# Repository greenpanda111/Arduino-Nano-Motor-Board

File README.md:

# Arduino-Nano-Motor-Board
A breakout board for an Arduino nano 33 BLE with motor controller and UART to serial port

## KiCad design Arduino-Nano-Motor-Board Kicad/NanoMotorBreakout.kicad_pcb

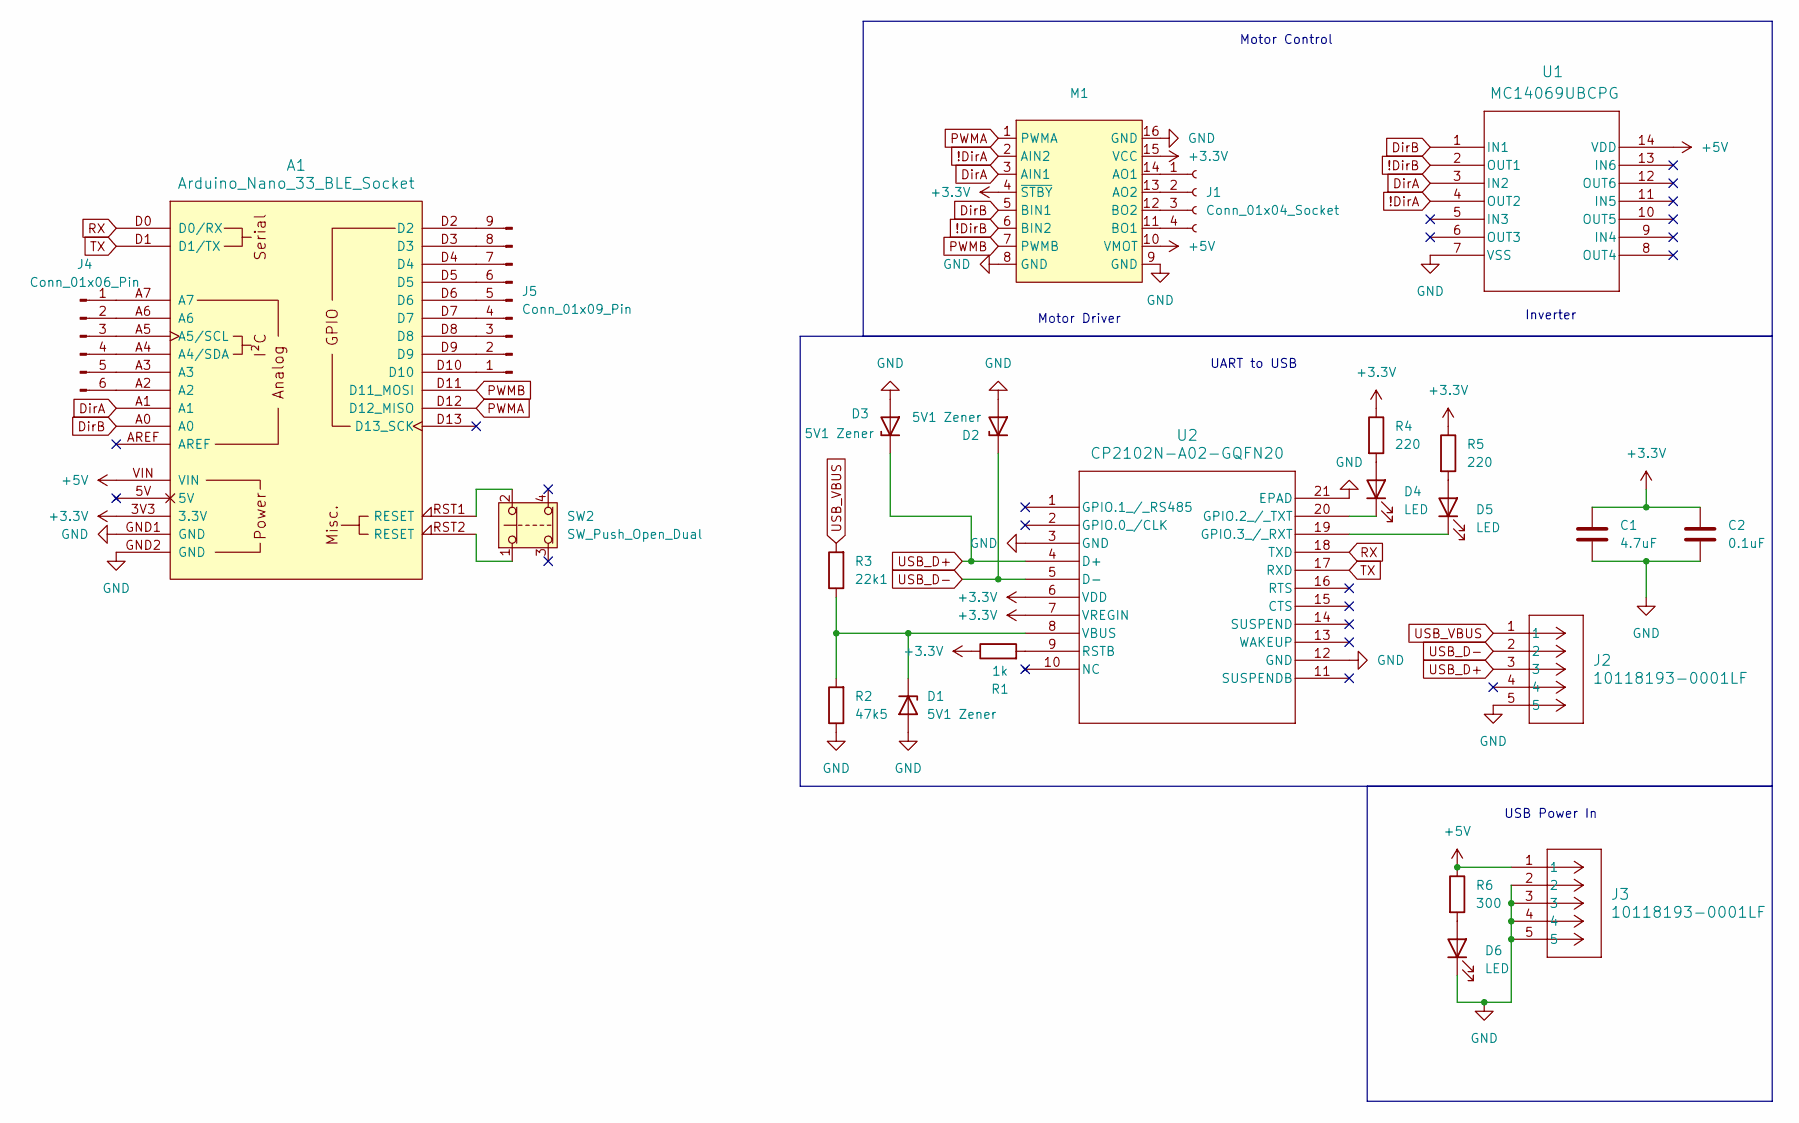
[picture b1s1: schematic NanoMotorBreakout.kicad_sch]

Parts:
A1: Arduino_Nano_33_BLE_Socket; Arduino_Nano_Every_Socket
C1: 4.7uF; CP_Radial_D5.0mm_P2.50mm
C2: 0.1uF; C_Disc_D3.8mm_W2.6mm_P2.50mm
D1, D2, D3: 5V1 Zener; D_DO-35_SOD27_P7.62mm_Horizontal
D4, D5, D6: LED; LED_D5.0mm
J1: Conn_01x04_Socket; PinSocket_1x04_P2.54mm_Vertical
J2, J3: 10118193-0001LF; CONN_47642-0001_MOL_fixed
J4: Conn_01x06_Pin; PinHeader_1x06_P2.54mm_Vertical
J5: Conn_01x09_Pin; PinHeader_1x09_P2.54mm_Vertical
M1: Pololu_MD08A_Motor_Driver
R1: 1k; R_Axial_DIN0207_L6.3mm_D2.5mm_P10.16mm_Horizontal
R2: 47k5; R_Axial_DIN0207_L6.3mm_D2.5mm_P10.16mm_Horizontal
R3: 22k1; R_Axial_DIN0207_L6.3mm_D2.5mm_P10.16mm_Horizontal
R4, R5: 220; R_Axial_DIN0207_L6.3mm_D2.5mm_P10.16mm_Horizontal
R6: 300; R_Axial_DIN0207_L6.3mm_D2.5mm_P10.16mm_Horizontal
SW2: SW_Push_Open_Dual; SW_PUSH_6mm_H4.3mm
U1: MC14069UBCPG; PDIP-14_ONS
U2: CP2102N-A02-GQFN20; QFN20_CP2102N_SIL

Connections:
!DirA: M1.2 (AIN2), U1.4 (OUT2)
!DirB: M1.6 (BIN2), U1.2 (OUT1)
+3.3V: A1.3V3 (3.3V), C1.1, C2.1, M1.4 (~STBY), M1.15 (VCC), R1.1, R4.1, R5.1, U2.6 (VDD), U2.7 (VREGIN)
+5V: A1.VIN, J3.1, M1.10 (VMOT), R6.1, U1.14 (VDD); also elsewhere on the board
DirA: A1.A1, M1.3 (AIN1), U1.3 (IN2)
DirB: A1.A0, M1.5 (BIN1), U1.1 (IN1)
GND: A1.GND1 (GND), A1.GND2 (GND), C1.2, C2.2, D1.2 (A), D2.2 (A), D3.2 (A), D6.1 (K), J2.5, J3.2, J3.3, J3.4, J3.5, M1.8 (GND), M1.9 (GND), M1.16 (GND), R2.1, U1.7 (VSS), U2.3 (GND), U2.12 (GND), U2.21 (EPAD); also elsewhere on the board
unnamed: A1.A4 (A4/SDA), J4.4
unnamed: A1.A5 (A5/SCL), J4.3
unnamed: A1.RST1 (RESET), SW2.2
unnamed: A1.RST2 (RESET), SW2.1
unnamed: D1.1 (K), R2.2, R3.1, U2.8 (VBUS)
unnamed: D4.2 (A), R4.2
unnamed: D4.1 (K), U2.20 (GPIO.2_/_TXT)
unnamed: D5.2 (A), R5.2
unnamed: D5.1 (K), U2.19 (GPIO.3_/_RXT)
unnamed: D6.2 (A), R6.2
unnamed: J1.1, M1.14 (AO1)
unnamed: J1.2, M1.13 (AO2)
unnamed: J1.3, M1.12 (BO2)
unnamed: J1.4, M1.11 (BO1)
unnamed: A1.A7, J4.1
unnamed: A1.A6, J4.2
unnamed: A1.A3, J4.5
unnamed: A1.A2, J4.6
unnamed: A1.D10, J5.1
unnamed: A1.D9, J5.2
unnamed: A1.D8, J5.3
unnamed: A1.D7, J5.4
unnamed: A1.D6, J5.5
unnamed: A1.D5, J5.6
unnamed: A1.D4, J5.7
unnamed: A1.D3, J5.8
unnamed: A1.D2, J5.9
unnamed: R1.2, U2.9 (RSTB)
PWMA: A1.D12 (D12_MISO), M1.1 (PWMA)
PWMB: A1.D11 (D11_MOSI), M1.7 (PWMB)
RX: A1.D0 (D0/RX), U2.18 (TXD)
TX: A1.D1 (D1/TX), U2.17 (RXD)
USB_D+: D3.1 (K), J2.3, U2.4 (D+); also elsewhere on the board
USB_D-: D2.1 (K), J2.2, U2.5 (D-); also elsewhere on the board
USB_VBUS: J2.1, R3.2; also elsewhere on the board

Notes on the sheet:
Motor Control
USB Power In
Motor Driver
UART to USB
Inverter

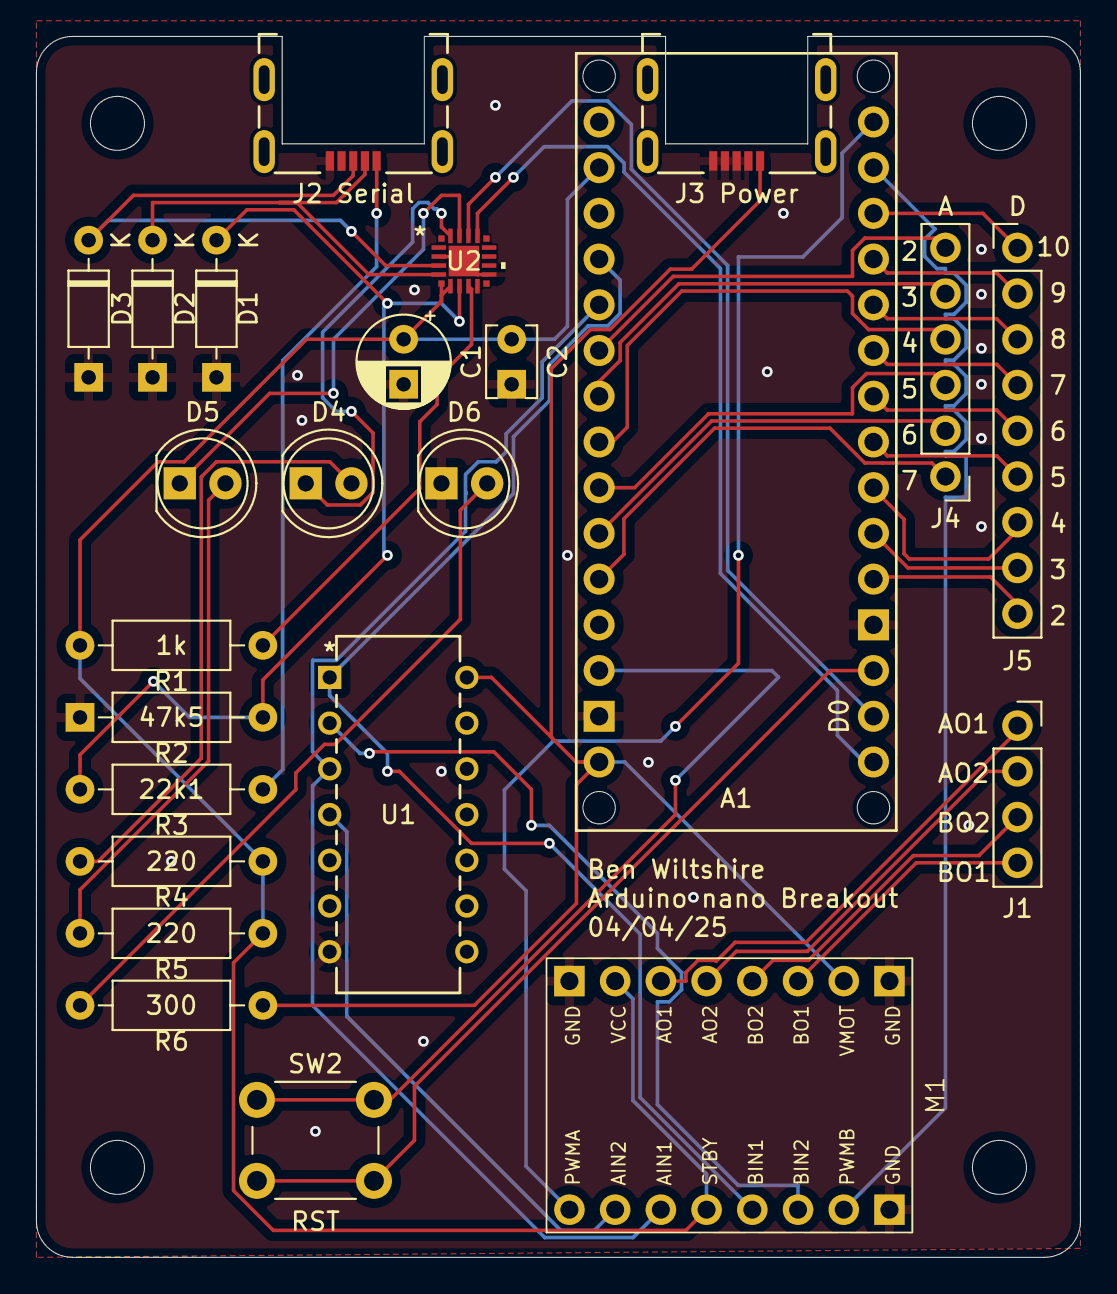
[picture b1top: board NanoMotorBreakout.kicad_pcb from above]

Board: 2 copper layers, 58.0 x 67.8 mm, 24 parts (0 on the bottom side), 42 nets.

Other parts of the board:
J2 Serial, J3 Power: 10118193-0001LF; CONN_47642-0001_MOL_fixed

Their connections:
+5V: J3 Power.1; also elsewhere on the board
GND: J2 Serial.5, J3 Power.2, J3 Power.3, J3 Power.4, J3 Power.5; also elsewhere on the board
USB_D+: J2 Serial.3; also elsewhere on the board
USB_D-: J2 Serial.2; also elsewhere on the board
USB_VBUS: J2 Serial.1; also elsewhere on the board

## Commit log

2025-04-04 PCB files initial commit
2025-04-04 Board Image Added
2025-04-06 Folder renamed
2025-04-06 Exports
